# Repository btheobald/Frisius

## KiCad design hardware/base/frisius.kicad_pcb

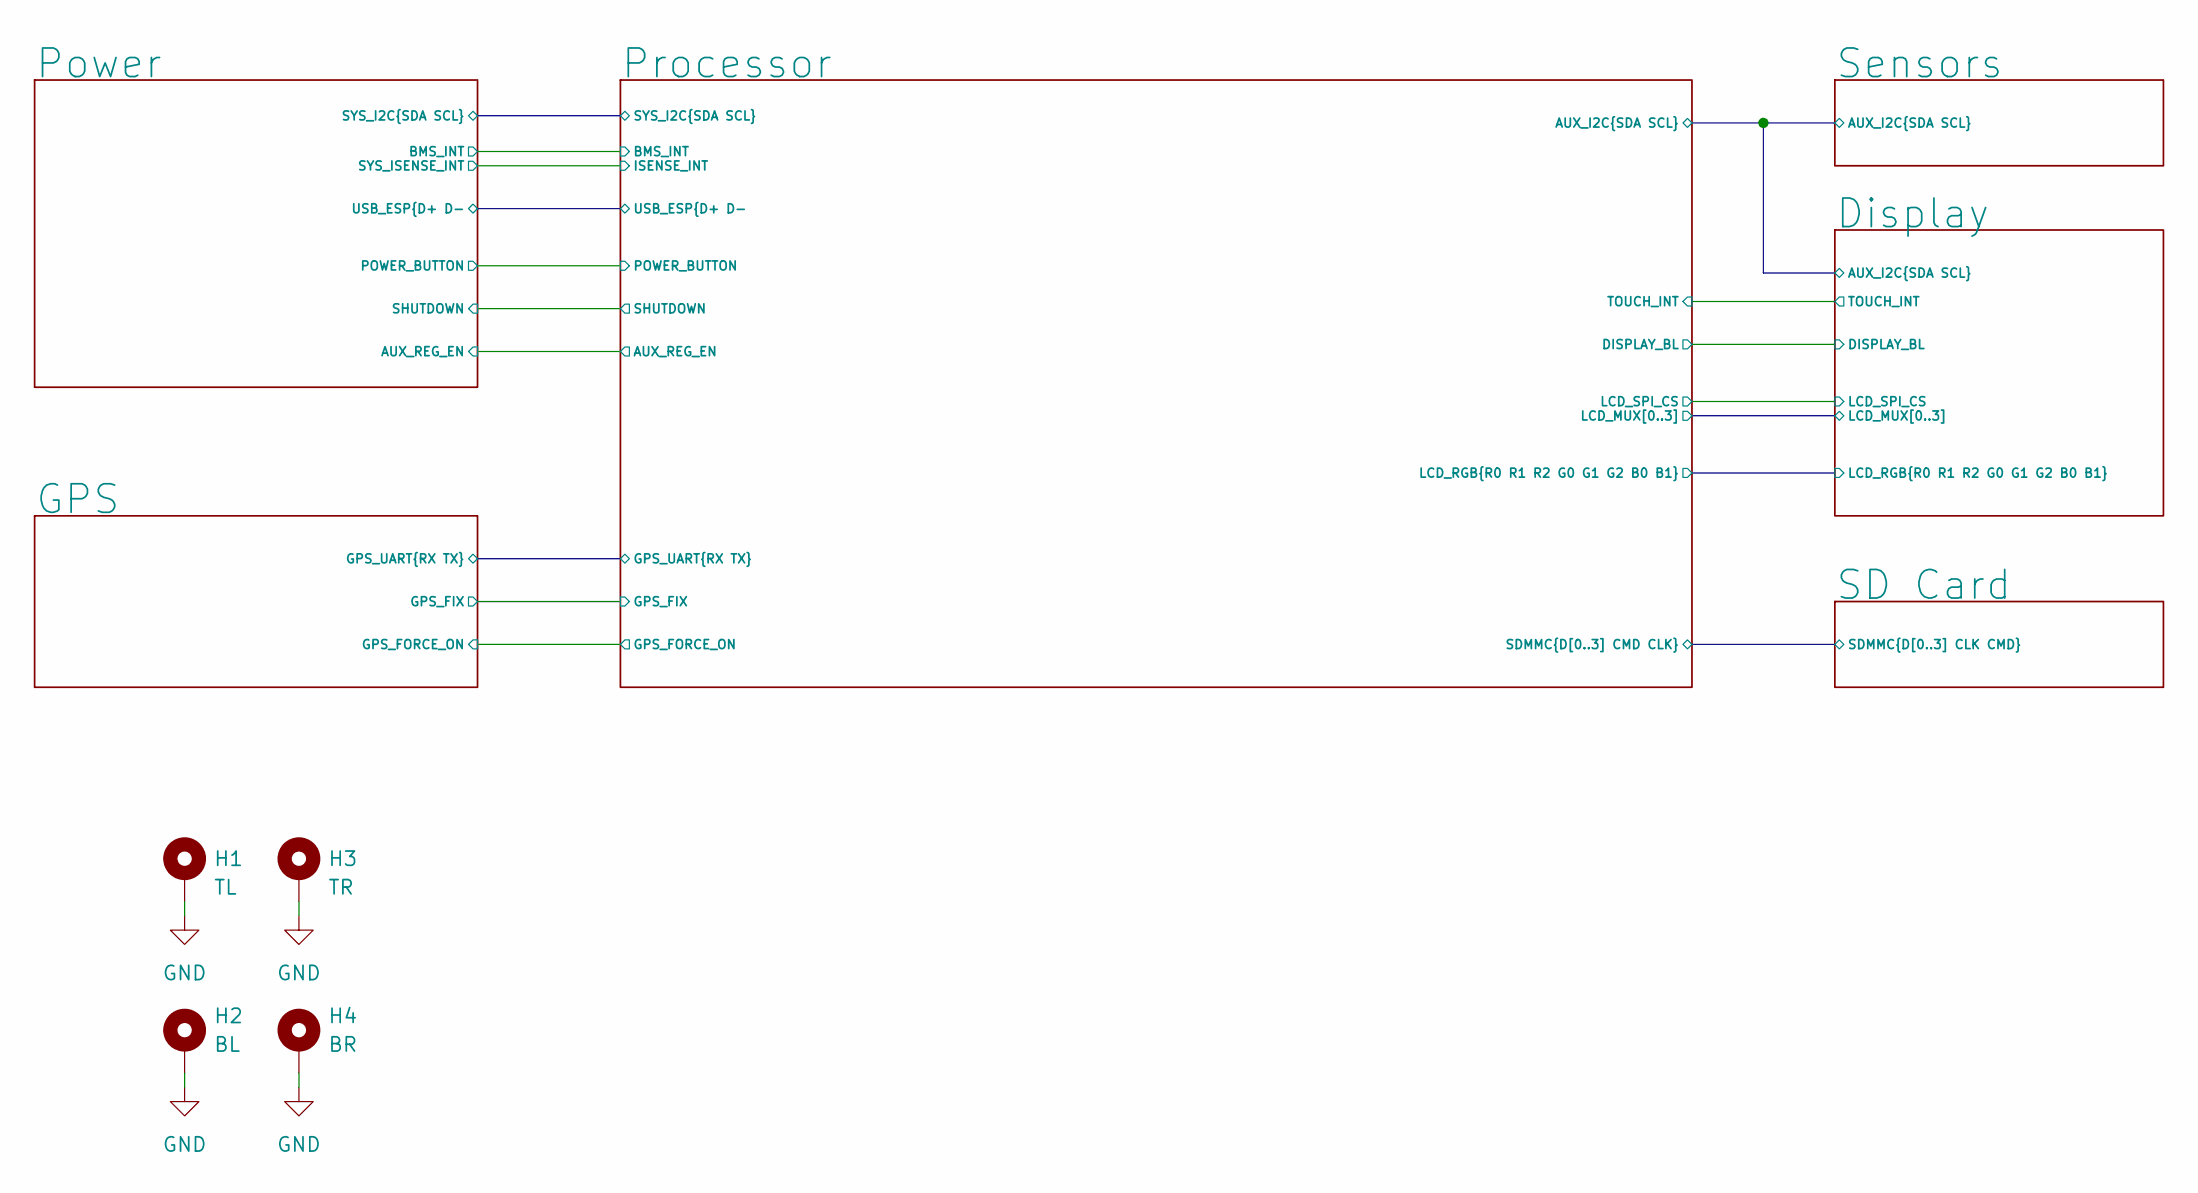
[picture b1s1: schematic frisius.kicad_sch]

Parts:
H1: TL; Mounting_Wuerth_WA-SMSI-M1.6_H2mm_9774020633
H2: BL; Mounting_Wuerth_WA-SMSI-M1.6_H2mm_9774020633
H3: TR; Mounting_Wuerth_WA-SMSI-M1.6_H2mm_9774020633
H4: BR; Mounting_Wuerth_WA-SMSI-M1.6_H2mm_9774020633

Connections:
GND: H1.1, H2.1, H3.1, H4.1; also elsewhere on the board

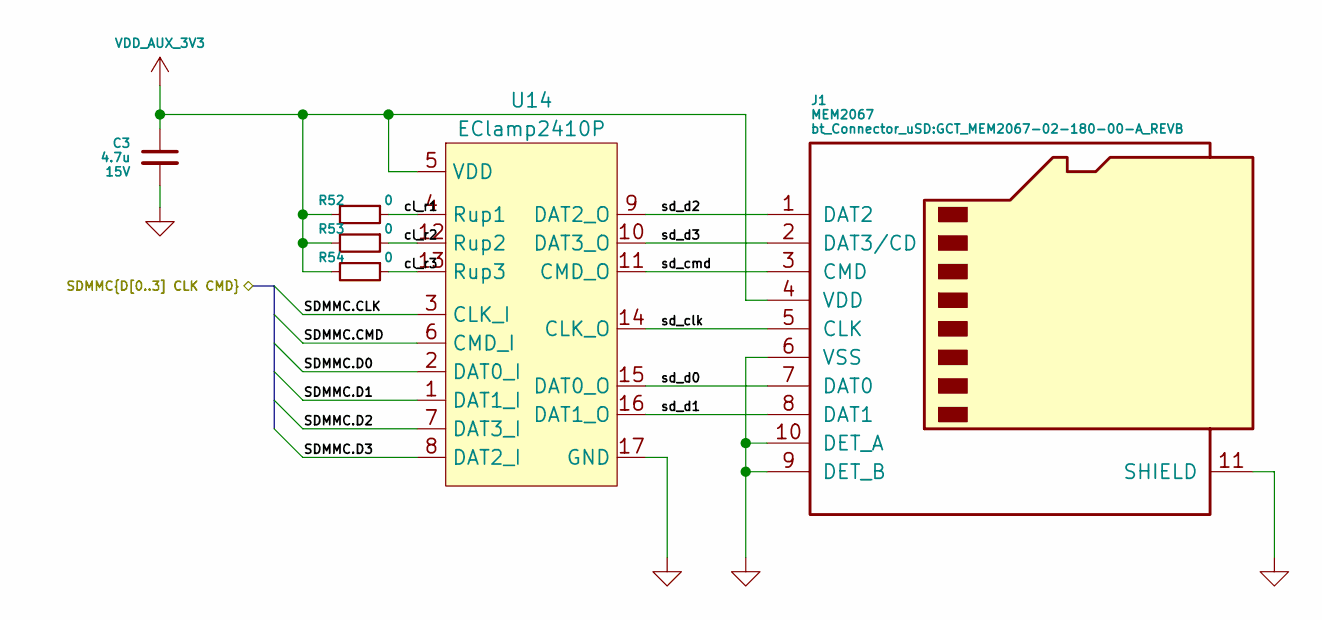
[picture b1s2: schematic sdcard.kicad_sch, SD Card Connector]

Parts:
C3: 4.7u; C_0603_1608Metric; Voltage 15V
J1: MEM2067; GCT_MEM2067-02-180-00-A_REVB
R52, R53, R54: 0; R_0402_1005Metric
U14: EClamp2410P; UDFN-16-4x1.6_P0.5mm_EP3x0.5mm

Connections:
/Processor/SDMMC.CLK: U14.3 (CLK_I); also elsewhere on the board
/Processor/SDMMC.CMD: U14.6 (CMD_I); also elsewhere on the board
/Processor/SDMMC.D0: U14.2 (DAT0_I); also elsewhere on the board
/Processor/SDMMC.D1: U14.1 (DAT1_I); also elsewhere on the board
/Processor/SDMMC.D2: U14.7 (DAT3_I); also elsewhere on the board
/Processor/SDMMC.D3: U14.8 (DAT2_I); also elsewhere on the board
/SD Card/cl_r1: R52.1, U14.4 (Rup1)
/SD Card/cl_r2: R53.1, U14.12 (Rup2)
/SD Card/cl_r3: R54.1, U14.13 (Rup3)
/SD Card/sd_clk: J1.5 (CLK), U14.14 (CLK_O)
/SD Card/sd_cmd: J1.3 (CMD), U14.11 (CMD_O)
/SD Card/sd_d0: J1.7 (DAT0), U14.15 (DAT0_O)
/SD Card/sd_d1: J1.8 (DAT1), U14.16 (DAT1_O)
/SD Card/sd_d2: J1.1 (DAT2), U14.9 (DAT2_O)
/SD Card/sd_d3: J1.2 (DAT3/CD), U14.10 (DAT3_O)
GND: C3.2, J1.6 (VSS), J1.9 (DET_B), J1.10 (DET_A), J1.11 (SHIELD), U14.17 (GND); also elsewhere on the board
VDD_AUX_3V3: C3.1, J1.4 (VDD), R52.2, R53.2, R54.2, U14.5 (VDD); also elsewhere on the board

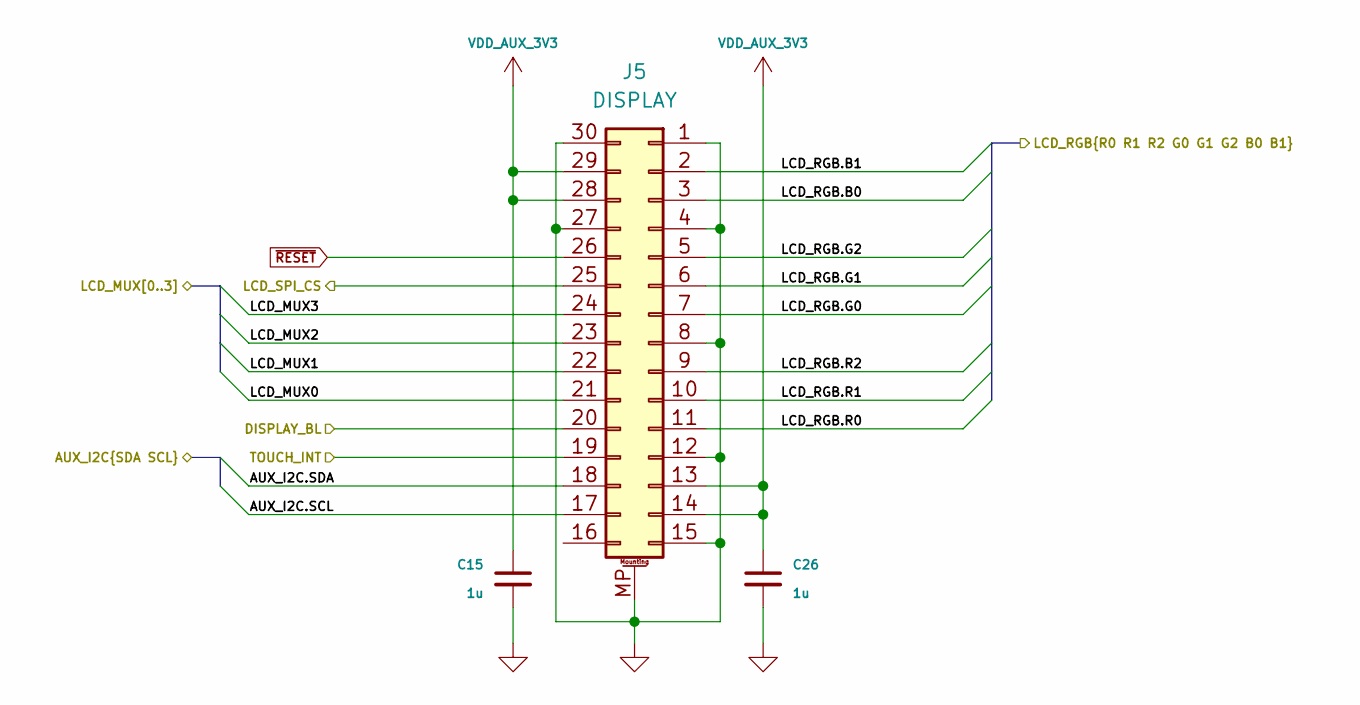
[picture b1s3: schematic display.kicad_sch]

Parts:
C15, C26: 1u; C_0603_1608Metric
J5: DISPLAY; 10132797-031100LF

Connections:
/Display/AUX_I2C.SCL: J5.17; also elsewhere on the board
/Display/AUX_I2C.SDA: J5.18; also elsewhere on the board
/Display/DISPLAY_BL: J5.20; also elsewhere on the board
/Display/LCD_MUX0: J5.21; also elsewhere on the board
/Display/LCD_MUX1: J5.22; also elsewhere on the board
/Display/LCD_MUX2: J5.23; also elsewhere on the board
/Display/LCD_MUX3: J5.24; also elsewhere on the board
/Display/LCD_RGB.B0: J5.3; also elsewhere on the board
/Display/LCD_RGB.B1: J5.2; also elsewhere on the board
/Display/LCD_RGB.G0: J5.7; also elsewhere on the board
/Display/LCD_RGB.G1: J5.6; also elsewhere on the board
/Display/LCD_RGB.G2: J5.5; also elsewhere on the board
/Display/LCD_RGB.R0: J5.11; also elsewhere on the board
/Display/LCD_RGB.R1: J5.10; also elsewhere on the board
/Display/LCD_RGB.R2: J5.9; also elsewhere on the board
/Display/LCD_SPI_CS: J5.25; also elsewhere on the board
/Display/TOUCH_INT: J5.19; also elsewhere on the board
GND: C15.2, C26.2, J5.1, J5.4, J5.8, J5.12, J5.15, J5.27, J5.30, J5.MP (MountPin); also elsewhere on the board
VDD_AUX_3V3: C15.1, C26.1, J5.13, J5.14, J5.28, J5.29; also elsewhere on the board
~RESET: J5.26; also elsewhere on the board

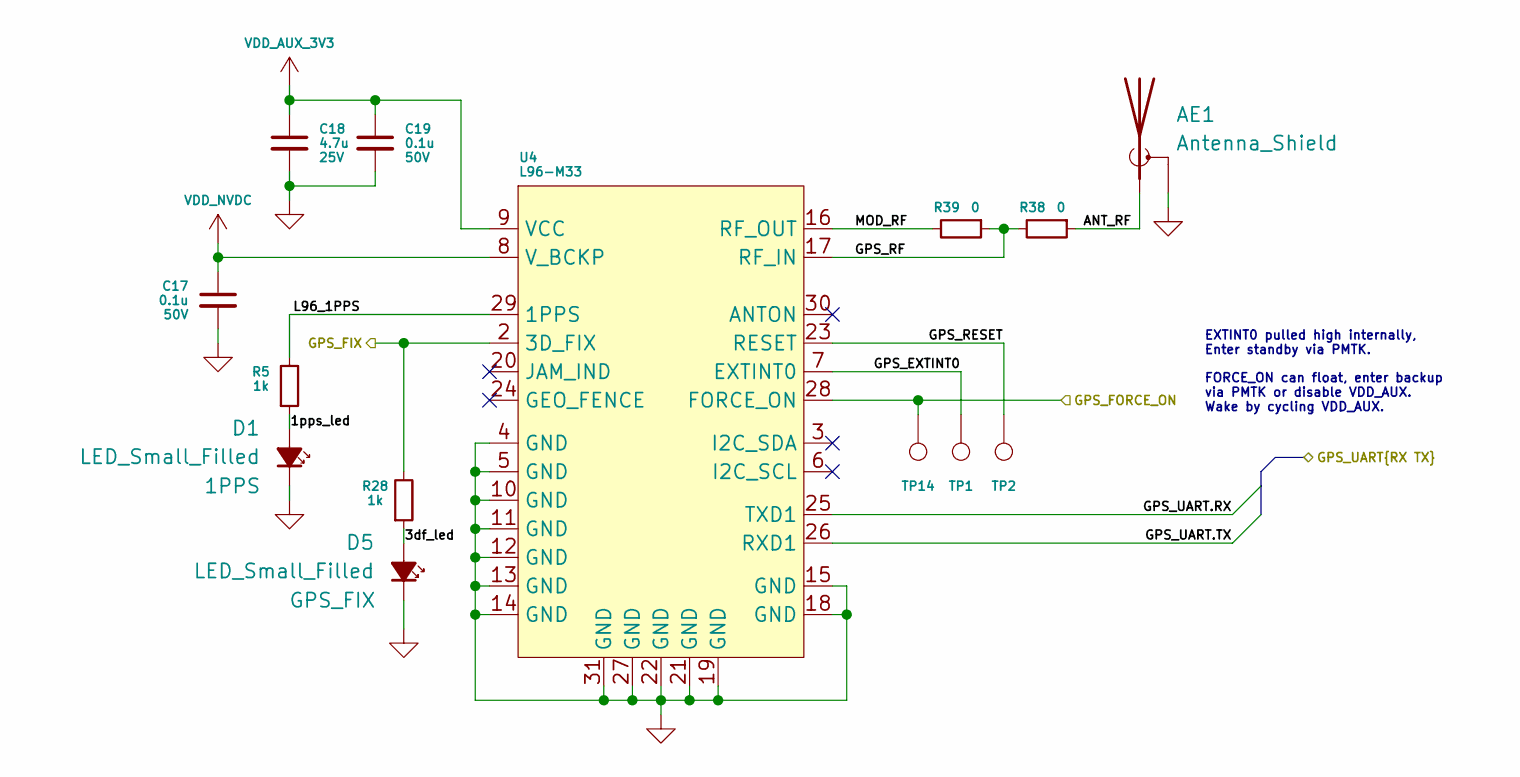
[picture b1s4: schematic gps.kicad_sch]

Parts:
AE1: Antenna_Shield; U.FL_Hirose_U.FL-R-SMT-1_Vertical
C17, C19: 0.1u; C_0402_1005Metric; Voltage 50V
C18: 4.7u; C_0603_1608Metric; Voltage 25V
D1, D5: LED_Small_Filled; LED_0603_1608Metric
R5, R28: 1k; R_0402_1005Metric
R38, R39: 0; R_0402_1005Metric
TP1, TP2, TP14: GPS_FON; TestPoint_Pad_D1.0mm
U4: L96-M33; Quectel_L96-M33

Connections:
/GPS/1pps_led: D1.2 (A), R5.1
/GPS/3df_led: D5.2 (A), R28.1
/GPS/ANT_RF: AE1.1 (A), R38.1
/GPS/GPS_EXTINT0: TP1.1, U4.7 (EXTINT0)
/GPS/GPS_FIX: R28.2, U4.2 (3D_FIX); also elsewhere on the board
/GPS/GPS_FORCE_ON: TP14.1, U4.28 (FORCE_ON); also elsewhere on the board
/GPS/GPS_RESET: TP2.1, U4.23 (RESET)
/GPS/GPS_RF: R38.2, R39.1, U4.17 (RF_IN)
/GPS/GPS_UART.RX: U4.25 (TXD1); also elsewhere on the board
/GPS/GPS_UART.TX: U4.26 (RXD1); also elsewhere on the board
/GPS/L96_1PPS: R5.2, U4.29 (1PPS)
/GPS/MOD_RF: R39.2, U4.16 (RF_OUT)
GND: AE1.2 (Shield), C17.2, C18.2, C19.2, D1.1 (K), D5.1 (K), U4.4 (GND), U4.5 (GND), U4.10 (GND), U4.11 (GND), U4.12 (GND), U4.13 (GND), U4.14 (GND), U4.15 (GND), U4.18 (GND), U4.19 (GND), U4.21 (GND), U4.22 (GND), U4.27 (GND), U4.31 (GND); also elsewhere on the board
VDD_AUX_3V3: C18.1, C19.1, U4.9 (VCC); also elsewhere on the board
VDD_NVDC: C17.1, U4.8 (V_BCKP); also elsewhere on the board

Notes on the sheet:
EXTINT0 pulled high internally, Enter standby via PMTK.
FORCE_ON can float, enter backup via PMTK or disable VDD_AUX. Wake by cycling VDD_AUX.

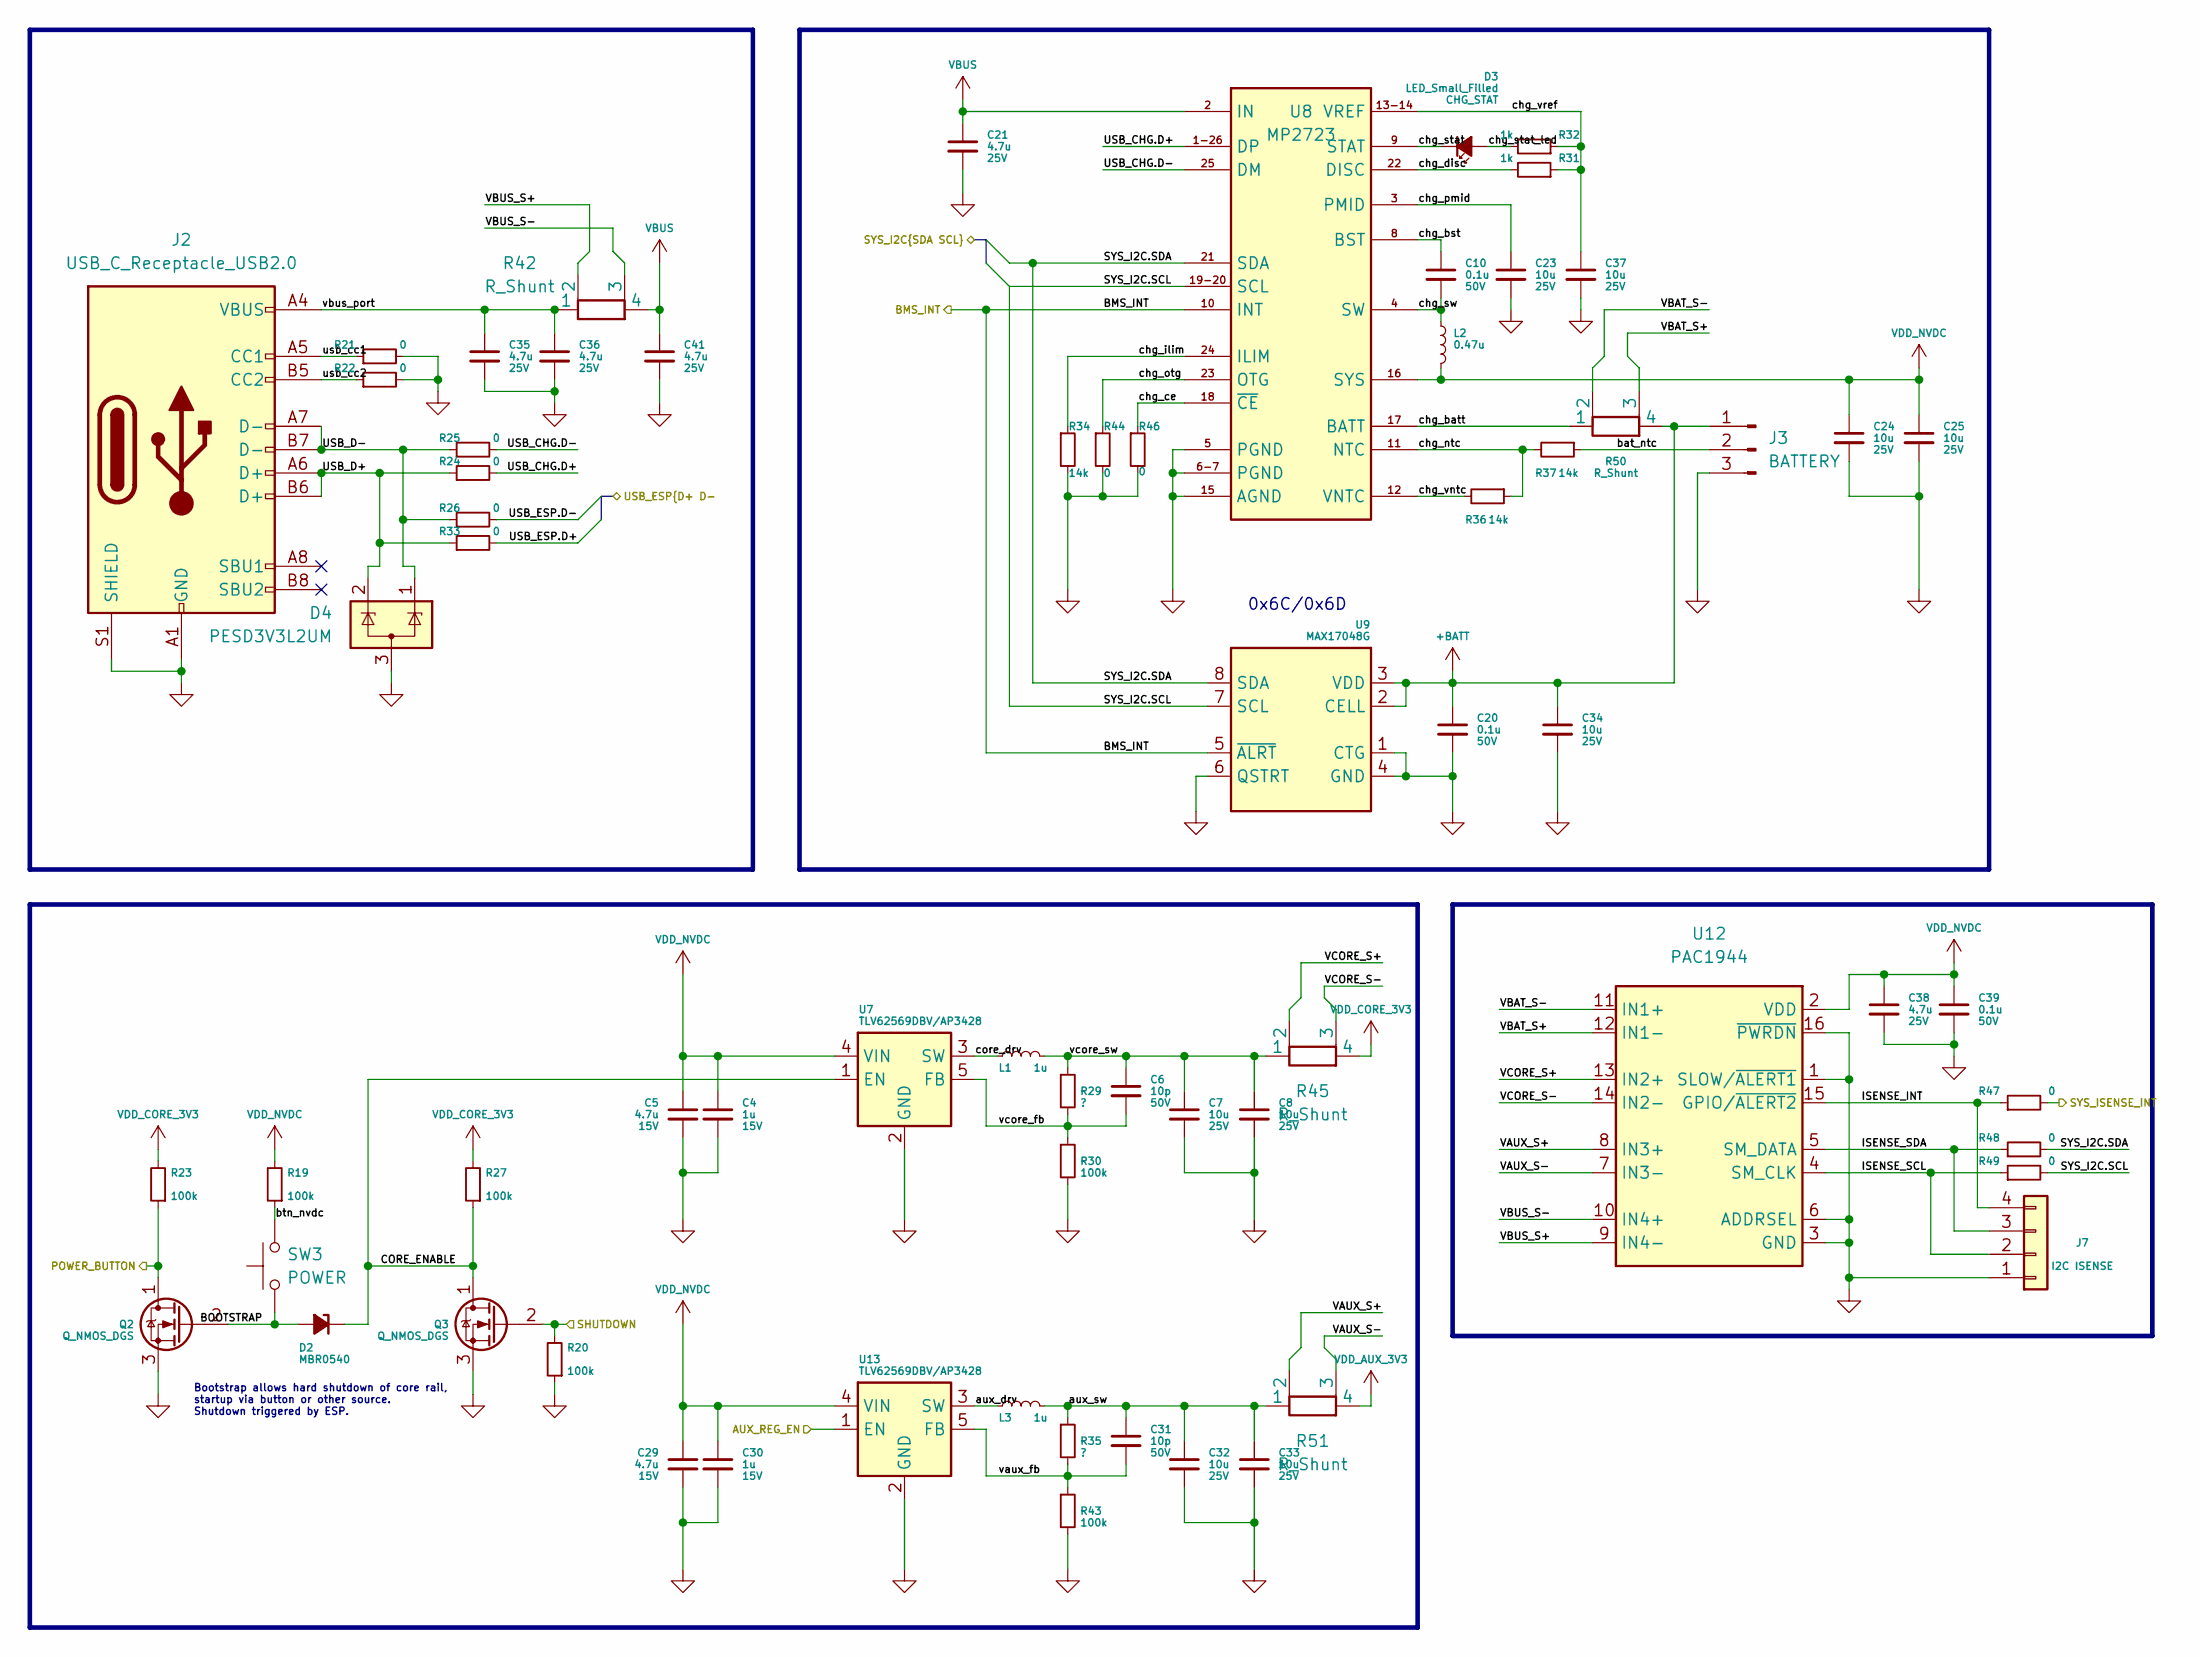
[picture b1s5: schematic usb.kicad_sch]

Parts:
C4, C30: 1u; C_0603_1608Metric; Voltage 15V
C5, C29: 4.7u; C_0603_1608Metric; Voltage 15V
C6, C31: 10p; C_0402_1005Metric; Voltage 50V
C7, C8, C23, C24, C25, C32, C33, C34, C37: 10u; C_0603_1608Metric; Voltage 25V
C10, C20, C39: 0.1u; C_0402_1005Metric; Voltage 50V
C21, C35, C36, C38, C41: 4.7u; C_0603_1608Metric; Voltage 25V
D2: MBR0540; D_SOD-123
D3: LED_Small_Filled; LED_0603_1608Metric
D4: PESD3V3L2UM; SOT-23
J2: USB_C_Receptacle_USB2.0; USB_C_Receptacle_HRO_TYPE-C-31-M-12
J3: BATTERY; PinHeader_1x03_P1.27mm_Vertical
J7: I2C ISENSE; PinHeader_1x04_P1.27mm_Vertical
L1, L3: 1u; L_Wuerth_MAPI-2510
L2: 0.47u; L_Wuerth_MAPI-2510
Q2, Q3: Q_NMOS_DGS; SOT-323_SC-70
R19, R20, R23, R27, R30, R43: 100k; R_0402_1005Metric
R21, R22, R24, R25, R26, R33, R44, R46, R47, R48, R49: 0; R_0402_1005Metric
R29, R35: ?; R_0402_1005Metric
R31, R32: 1k; R_0402_1005Metric
R34, R36, R37: 14k; R_0402_1005Metric
R42, R45, R50, R51: R_Shunt; R_0805_4WKelvin
SW3: POWER; SW_SPST_B3U-1000P
U7, U13: TLV62569DBV/AP3428; SOT-23-5
U8: MP2723; MP_QFN-26-3.5x3.5_P0.45mm
U9: MAX17048G; TDFN-8-1EP_2x2mm_P0.5mm_EP0.8x1.2mm
U12: PAC1944; UQFN-16-1EP_4x4mm_P0.65mm_EP2.7x2.7mm

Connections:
+BATT: C20.1, C34.1, J3.1, R50.4, U9.2 (CELL), U9.3 (VDD)
/Power/AUX_REG_EN: U13.1 (EN); also elsewhere on the board
/Power/BMS_INT: U8.10 (INT), U9.5 (~ALRT); also elsewhere on the board
/Power/BOOTSTRAP: D2.2 (A), Q2.2 (G), SW3.2
/Power/CORE_ENABLE: D2.1 (K), Q3.1 (D), R27.1, U7.1 (EN)
/Power/ISENSE_INT: J7.4, R47.1, U12.15 (GPIO/~ALERT2)
/Power/ISENSE_SCL: J7.2, R49.1, U12.4 (SM_CLK)
/Power/ISENSE_SDA: J7.3, R48.1, U12.5 (SM_DATA)
/Power/POWER_BUTTON: Q2.1 (D), R23.1; also elsewhere on the board
/Power/SHUTDOWN: Q3.2 (G), R20.2; also elsewhere on the board
/Power/SYS_I2C.SCL: R49.2, U8.19-20 (SCL), U9.7 (SCL); also elsewhere on the board
/Power/SYS_I2C.SDA: R48.2, U8.21 (SDA), U9.8 (SDA); also elsewhere on the board
/Power/SYS_ISENSE_INT: R47.2; also elsewhere on the board
/Power/USB_CHG.D+: R24.2, U8.1-26 (DP)
/Power/USB_CHG.D-: R25.2, U8.25 (DM)
/Power/USB_D+: D4.2 (K), J2.A6 (D+), J2.B6 (D+), R24.1, R33.1
/Power/USB_D-: D4.1 (K), J2.A7 (D-), J2.B7 (D-), R25.1, R26.1
/Power/USB_ESP.D+: R33.2; also elsewhere on the board
/Power/USB_ESP.D-: R26.2; also elsewhere on the board
/Power/VAUX_S+: R51.2, U12.8 (IN3+)
/Power/VAUX_S-: R51.3, U12.7 (IN3-)
/Power/VBAT_S+: R50.3, U12.12 (IN1-)
/Power/VBAT_S-: R50.2, U12.11 (IN1+)
/Power/VBUS_S+: R42.2, U12.9 (IN4-)
/Power/VBUS_S-: R42.3, U12.10 (IN4+)
/Power/VCORE_S+: R45.2, U12.13 (IN2+)
/Power/VCORE_S-: R45.3, U12.14 (IN2-)
/Power/aux_drv: L3.1, U13.3 (SW)
/Power/aux_sw: C31.1, C32.1, C33.1, L3.2, R35.1, R51.1
/Power/bat_ntc: J3.2, R37.1
/Power/btn_nvdc: R19.1, SW3.1
/Power/chg_batt: R50.1, U8.17 (BATT)
/Power/chg_bst: C10.1, U8.8 (BST)
/Power/chg_ce: R46.1, U8.18 (~CE)
/Power/chg_disc: R31.2, U8.22 (DISC)
/Power/chg_ilim: R34.1, U8.24 (ILIM)
/Power/chg_ntc: R36.1, R37.2, U8.11 (NTC)
/Power/chg_otg: R44.1, U8.23 (OTG)
/Power/chg_pmid: C23.1, U8.3 (PMID)
/Power/chg_stat: D3.1 (K), U8.9 (STAT)
/Power/chg_stat_led: D3.2 (A), R32.2
/Power/chg_sw: C10.2, L2.1, U8.4 (SW)
/Power/chg_vntc: R36.2, U8.12 (VNTC)
/Power/chg_vref: C37.1, R31.1, R32.1, U8.13-14 (VREF)
/Power/core_drv: L1.1, U7.3 (SW)
/Power/usb_cc1: J2.A5 (CC1), R21.1
/Power/usb_cc2: J2.B5 (CC2), R22.1
/Power/vaux_fb: C31.2, R35.2, R43.1, U13.5 (FB)
/Power/vbus_port: C35.1, C36.1, J2.A4 (VBUS), J2.A9 (VBUS), J2.B4 (VBUS), J2.B9 (VBUS), R42.1
/Power/vcore_fb: C6.2, R29.2, R30.1, U7.5 (FB)
/Power/vcore_sw: C6.1, C7.1, C8.1, L1.2, R29.1, R45.1
GND: C4.2, C5.2, C7.2, C8.2, C20.2, C21.2, C23.2, C24.2, C25.2, C29.2, C30.2, C32.2, C33.2, C34.2, C35.2, C36.2, C37.2, C38.2, C39.2, C41.2, D4.3 (A), J2.A1 (GND), J2.A12 (GND), J2.B1 (GND), J2.B12 (GND), J2.S1 (SHIELD), J3.3, J7.1, Q2.3 (S), Q3.3 (S), R20.1, R21.2, R22.2, R30.2, R34.2, R43.2, R44.2, R46.2, U7.2 (GND), U8.5 (PGND), U8.6-7 (PGND), U8.15 (AGND), U9.1 (CTG), U9.4 (GND), U9.6 (QSTRT), U9.9 (PAD), U12.1 (SLOW/~ALERT1), U12.3 (GND), U12.6 (ADDRSEL), U12.16 (~PWRDN), U12.17 (GND), U13.2 (GND); also elsewhere on the board
VBUS: C21.1, C41.1, R42.4, U8.2 (IN)
VDD_AUX_3V3: R51.4; also elsewhere on the board
VDD_CORE_3V3: R23.2, R27.2, R45.4; also elsewhere on the board
VDD_NVDC: C4.1, C5.1, C24.1, C25.1, C29.1, C30.1, C38.1, C39.1, L2.2, R19.2, U7.4 (VIN), U8.16 (SYS), U12.2 (VDD), U13.4 (VIN); also elsewhere on the board

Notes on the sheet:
Bootstrap allows hard shutdown of core rail, startup via button or other source. Shutdown triggered by ESP.
0x6C/0x6D

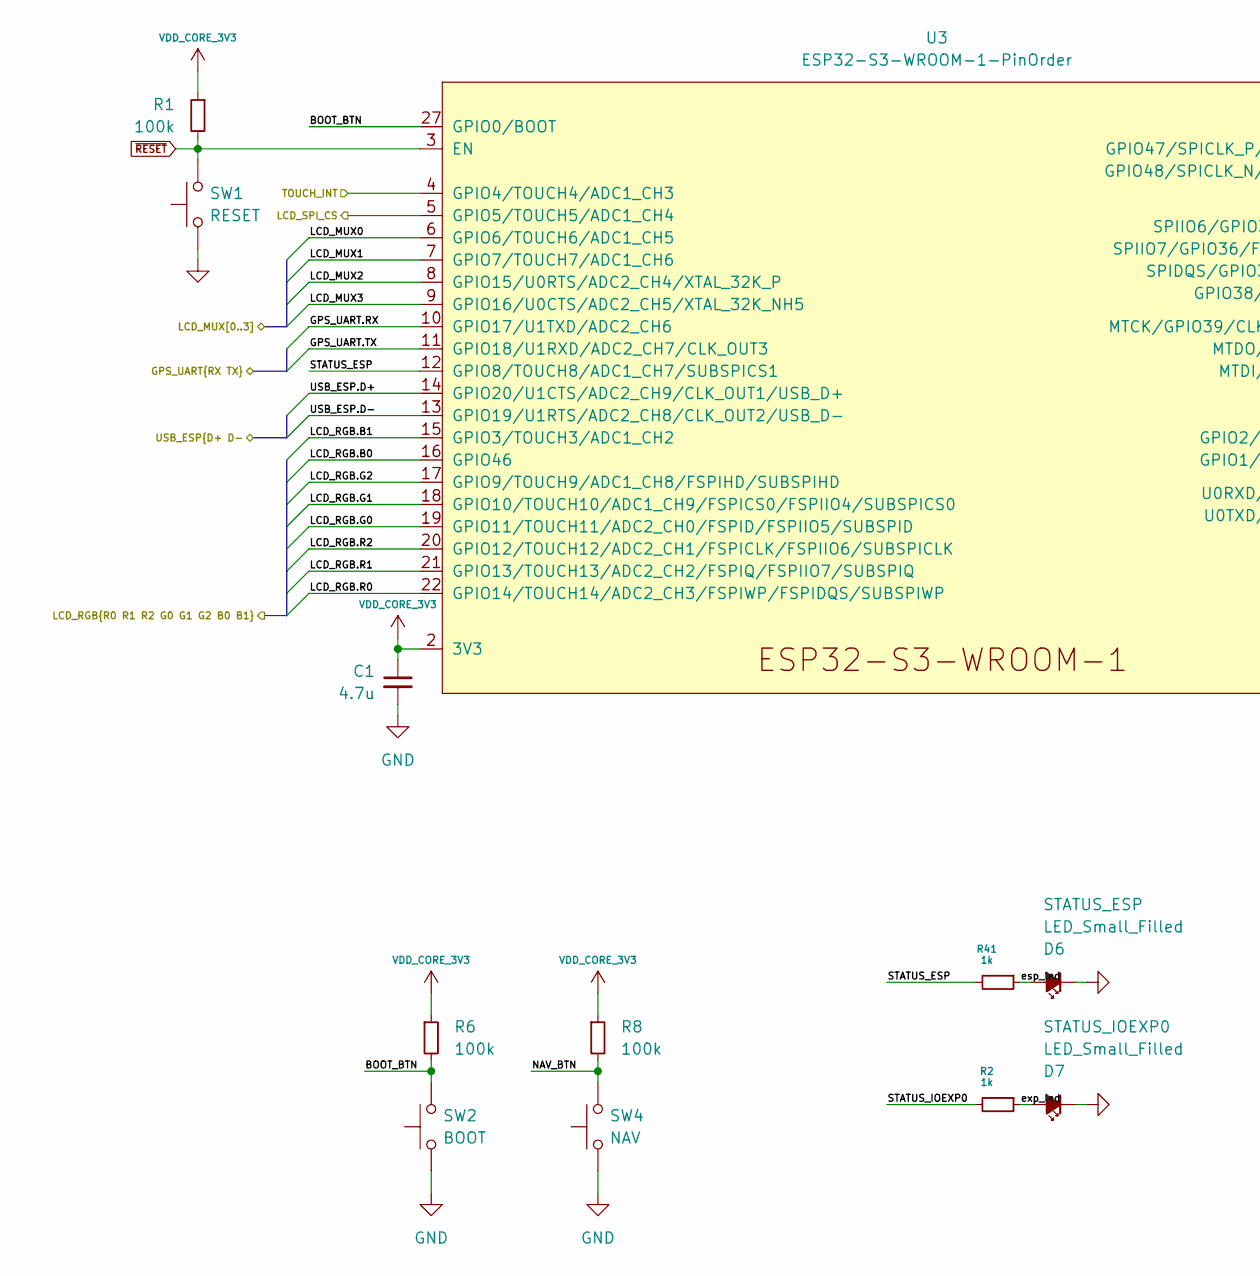
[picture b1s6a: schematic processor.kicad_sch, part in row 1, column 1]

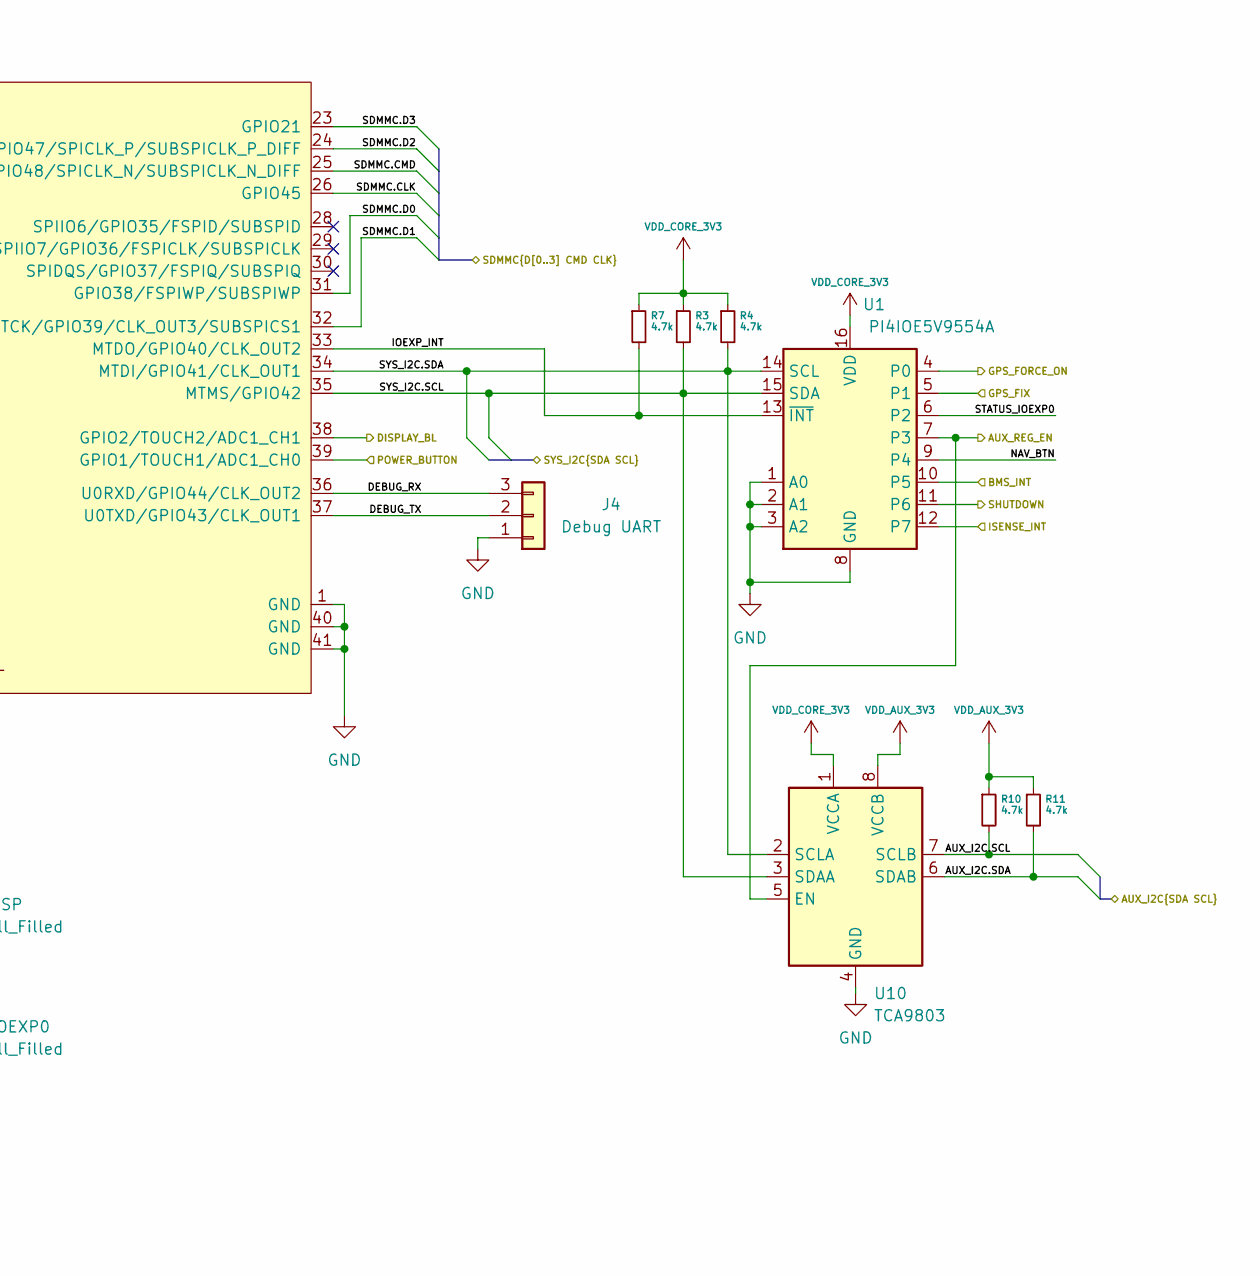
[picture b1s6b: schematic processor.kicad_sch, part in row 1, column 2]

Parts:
C1: 4.7u; C_0603_1608Metric
D6, D7: LED_Small_Filled; LED_0603_1608Metric
J4: Debug UART; PinHeader_1x03_P2.54mm_Vertical
R1, R6, R8: 100k; R_0402_1005Metric
R2, R41: 1k; R_0402_1005Metric
R3, R4, R7, R10, R11: 4.7k; R_0402_1005Metric
SW1: RESET; SW_SPST_B3U-1000P
SW2: BOOT; SW_SPST_B3U-1000P
SW4: NAV; SW_SPST_B3U-1000P
U1: PI4IOE5V9554A; TSSOP-16_4.4x5mm_P0.65mm
U3: ESP32-S3-WROOM-1-PinOrder; ESP32-S3-WROOM-1U
U10: TCA9803; VSSOP-8_3.0x3.0mm_P0.65mm

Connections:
/Display/AUX_I2C.SCL: R10.2, U10.7 (SCLB); also elsewhere on the board
/Display/AUX_I2C.SDA: R11.2, U10.6 (SDAB); also elsewhere on the board
/Display/DISPLAY_BL: U3.38 (GPIO2/TOUCH2/ADC1_CH1); also elsewhere on the board
/Display/LCD_MUX0: U3.6 (GPIO6/TOUCH6/ADC1_CH5); also elsewhere on the board
/Display/LCD_MUX1: U3.7 (GPIO7/TOUCH7/ADC1_CH6); also elsewhere on the board
/Display/LCD_MUX2: U3.8 (GPIO15/U0RTS/ADC2_CH4/XTAL_32K_P); also elsewhere on the board
/Display/LCD_MUX3: U3.9 (GPIO16/U0CTS/ADC2_CH5/XTAL_32K_NH5); also elsewhere on the board
/Display/LCD_RGB.B0: U3.16 (GPIO46); also elsewhere on the board
/Display/LCD_RGB.B1: U3.15 (GPIO3/TOUCH3/ADC1_CH2); also elsewhere on the board
/Display/LCD_RGB.G0: U3.19 (GPIO11/TOUCH11/ADC2_CH0/FSPID/FSPIIO5/S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); also elsewhere on the board
/Display/LCD_RGB.G1: U3.18 (GPIO10/TOUCH10/ADC1_CH9/FSPICS0/FSPIIO4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); also elsewhere on the board
/Display/LCD_RGB.G2: U3.17 (GPIO9/TOUCH9/ADC1_CH8/FSPIHD/SUBSPIHD); also elsewhere on the board
/Display/LCD_RGB.R0: U3.22 (GPIO14/TOUCH14/ADC2_CH3/FSPIWP/FSPIDQS/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); also elsewhere on the board
/Display/LCD_RGB.R1: U3.21 (GPIO13/TOUCH13/ADC2_CH2/FSPIQ/FSPIIO7/S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); also elsewhere on the board
/Display/LCD_RGB.R2: U3.20 (GPIO12/TOUCH12/ADC2_CH1/FSPICLK/FSPIIO6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); also elsewhere on the board
/Display/LCD_SPI_CS: U3.5 (GPIO5/TOUCH5/ADC1_CH4); also elsewhere on the board
/Display/TOUCH_INT: U3.4 (GPIO4/TOUCH4/ADC1_CH3); also elsewhere on the board
/GPS/GPS_FIX: U1.5 (P1); also elsewhere on the board
/GPS/GPS_FORCE_ON: U1.4 (P0); also elsewhere on the board
/GPS/GPS_UART.RX: U3.10 (GPIO17/U1TXD/ADC2_CH6); also elsewhere on the board
/GPS/GPS_UART.TX: U3.11 (GPIO18/U1RXD/ADC2_CH7/CLK_OUT3); also elsewhere on the board
/Power/AUX_REG_EN: U1.7 (P3), U10.5 (EN); also elsewhere on the board
/Power/BMS_INT: U1.10 (P5); also elsewhere on the board
/Power/POWER_BUTTON: U3.39 (GPIO1/TOUCH1/ADC1_CH0); also elsewhere on the board
/Power/SHUTDOWN: U1.11 (P6); also elsewhere on the board
/Power/SYS_I2C.SCL: R3.2, U1.15 (SDA), U3.35 (MTMS/GPIO42), U10.3 (SDAA); also elsewhere on the board
/Power/SYS_I2C.SDA: R4.2, U1.14 (SCL), U3.34 (MTDI/GPIO41/CLK_OUT1), U10.2 (SCLA); also elsewhere on the board
/Power/SYS_ISENSE_INT: U1.12 (P7); also elsewhere on the board
/Power/USB_ESP.D+: U3.14 (GPIO20/U1CTS/ADC2_CH9/CLK_OUT1/USB_D+); also elsewhere on the board
/Power/USB_ESP.D-: U3.13 (GPIO19/U1RTS/ADC2_CH8/CLK_OUT2/USB_D-); also elsewhere on the board
/Processor/BOOT_BTN: R6.2, SW2.2, U3.27 (GPIO0/BOOT)
/Processor/DEBUG_RX: J4.3, U3.36 (U0RXD/GPIO44/CLK_OUT2)
/Processor/DEBUG_TX: J4.2, U3.37 (U0TXD/GPIO43/CLK_OUT1)
/Processor/IOEXP_INT: R7.2, U1.13 (~INT), U3.33 (MTDO/GPIO40/CLK_OUT2)
/Processor/NAV_BTN: R8.2, SW4.2, U1.9 (P4)
/Processor/SDMMC.CLK: U3.26 (GPIO45); also elsewhere on the board
/Processor/SDMMC.CMD: U3.25 (GPIO48/SPICLK_N/SUBSPICLK_N_DIFF); also elsewhere on the board
/Processor/SDMMC.D0: U3.31 (GPIO38/FSPIWP/SUBSPIWP); also elsewhere on the board
/Processor/SDMMC.D1: U3.32 (MTCK/GPIO39/CLK_OUT3/SUBSPICS1); also elsewhere on the board
/Processor/SDMMC.D2: U3.24 (GPIO47/SPICLK_P/SUBSPICLK_P_DIFF); also elsewhere on the board
/Processor/SDMMC.D3: U3.23 (GPIO21); also elsewhere on the board
/Processor/STATUS_ESP: R41.2, U3.12 (GPIO8/TOUCH8/ADC1_CH7/SUBSPICS1)
/Processor/STATUS_IOEXP0: R2.2, U1.6 (P2)
/Processor/esp_led: D6.2 (A), R41.1
/Processor/exp_led: D7.2 (A), R2.1
GND: C1.2, D6.1 (K), D7.1 (K), J4.1, SW1.1, SW2.1, SW4.1, U1.1 (A0), U1.2 (A1), U1.3 (A2), U1.8 (GND), U3.1 (GND), U3.40 (GND), U3.41 (GND), U10.4 (GND); also elsewhere on the board
VDD_AUX_3V3: R10.1, R11.1, U10.8 (VCCB); also elsewhere on the board
VDD_CORE_3V3: C1.1, R1.1, R3.1, R4.1, R6.1, R7.1, R8.1, U1.16 (VDD), U3.2 (3V3), U10.1 (VCCA); also elsewhere on the board
~RESET: R1.2, SW1.2, U3.3 (EN); also elsewhere on the board

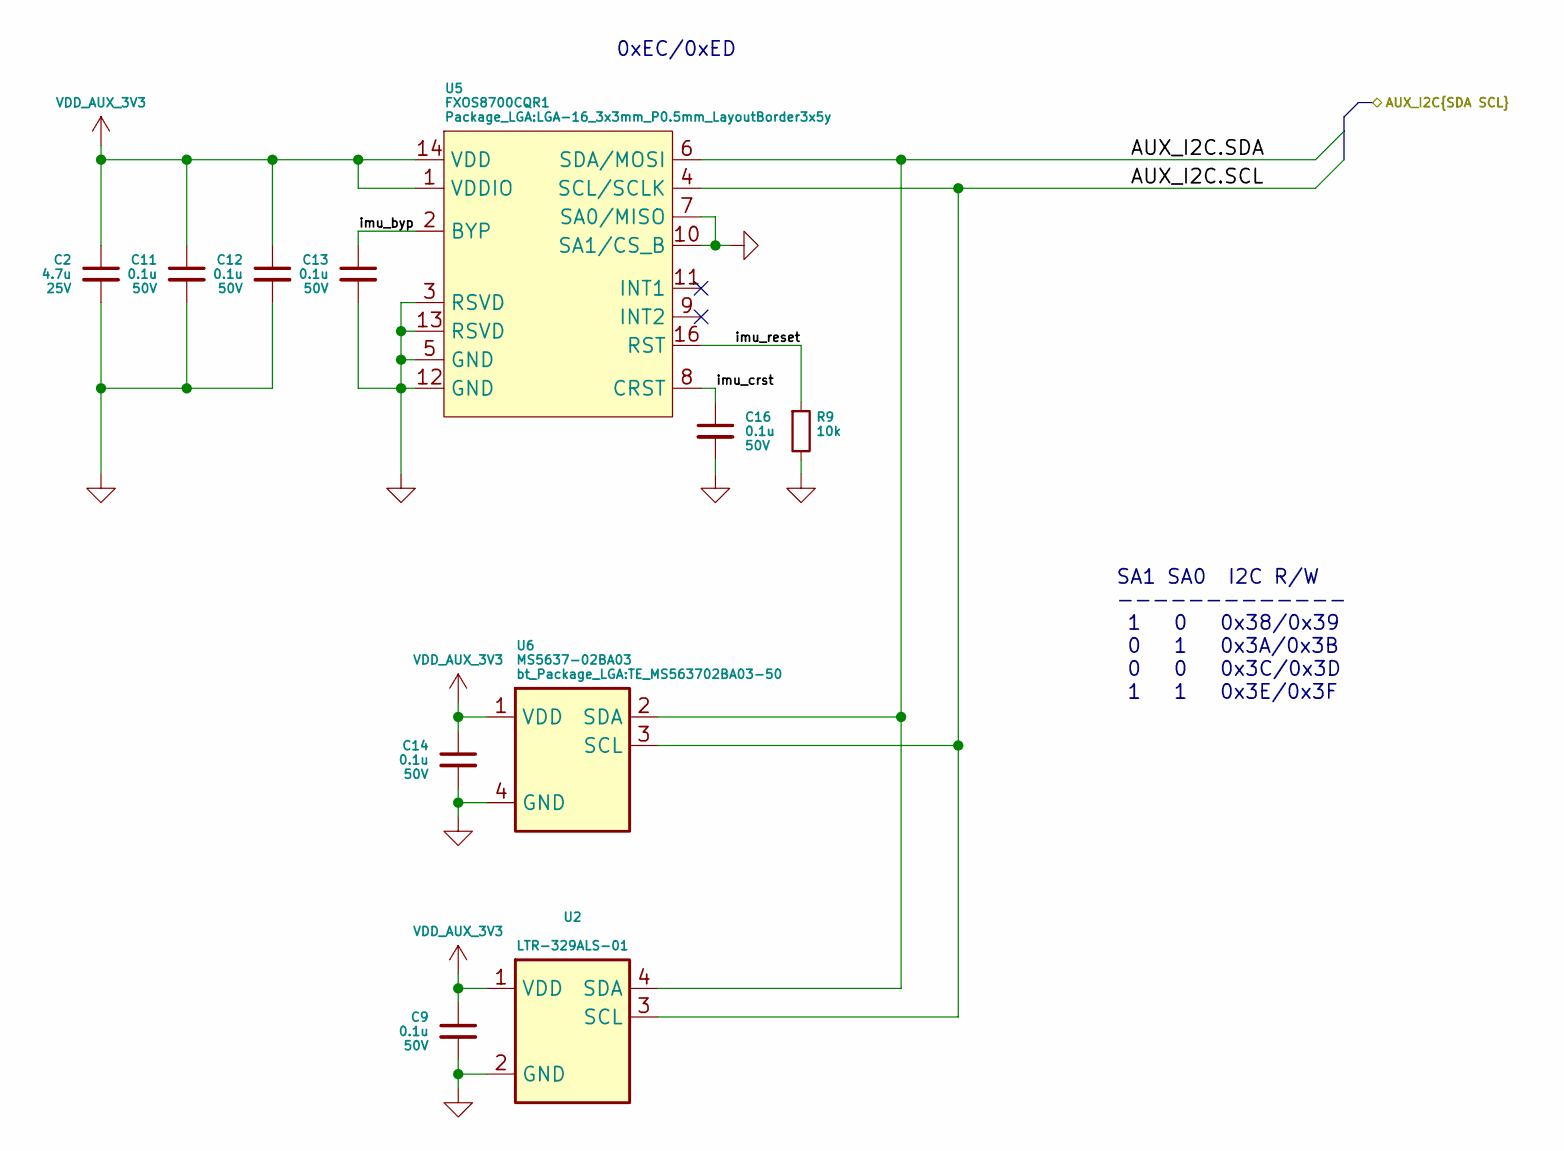
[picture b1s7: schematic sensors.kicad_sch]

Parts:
C2: 4.7u; C_0603_1608Metric; Voltage 25V
C9, C11, C12, C13, C14, C16: 0.1u; C_0402_1005Metric; Voltage 50V
R9: 10k; R_0402_1005Metric
U2: LTR-329ALS-01; VLGA-4_2x2.5mm_P1.65mm
U5: FXOS8700CQR1; LGA-16_3x3mm_P0.5mm_LayoutBorder3x5y
U6: MS5637-02BA03; TE_MS563702BA03-50

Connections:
/Display/AUX_I2C.SCL: U2.3 (SCL), U5.4 (SCL/SCLK), U6.3 (SCL); also elsewhere on the board
/Display/AUX_I2C.SDA: U2.4 (SDA), U5.6 (SDA/MOSI), U6.2 (SDA); also elsewhere on the board
/Sensors/imu_byp: C13.1, U5.2 (BYP)
/Sensors/imu_crst: C16.1, U5.8 (CRST)
/Sensors/imu_reset: R9.1, U5.16 (RST)
GND: C2.2, C9.2, C11.2, C12.2, C13.2, C14.2, C16.2, R9.2, U2.2 (GND), U5.3 (RSVD), U5.5 (GND), U5.7 (SA0/MISO), U5.10 (SA1/CS_B), U5.12 (GND), U5.13 (RSVD), U6.4 (GND); also elsewhere on the board
VDD_AUX_3V3: C2.1, C9.1, C11.1, C12.1, C14.1, U2.1 (VDD), U5.1 (VDDIO), U5.14 (VDD), U6.1 (VDD); also elsewhere on the board

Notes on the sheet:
0xEC/0xED
SA1 SA0 I2C R/W ------------- 1 0 0x38/0x39 0 1 0x3A/0x3B 0 0 0x3C/0x3D 1 1 0x3E/0x3F
